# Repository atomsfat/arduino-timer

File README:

Arduino timer
=============
This is a configurable timer using arduino, rtc (DS1307) and a lcd display
For debian and ubuntu install avr-compiler
```js
apt-get install avrdude binutils-avr gcc-avr avr-libc gdb-avr
```
Install eclipse-cpp
Configure the project:
File>Project>Makefile with existing source
Install arduino-022
Change the following in the Makefile
ARDUINO_PATH
AVRDUDE_PORT
AVR_TOOLS_PATH

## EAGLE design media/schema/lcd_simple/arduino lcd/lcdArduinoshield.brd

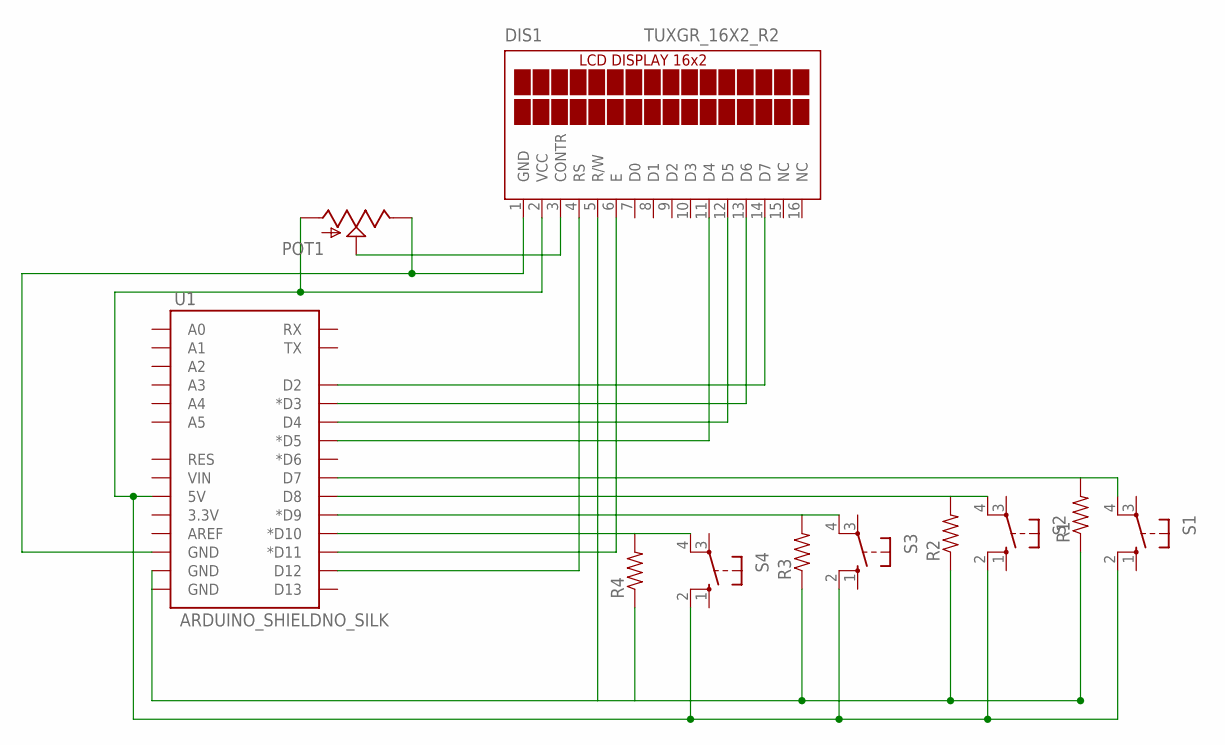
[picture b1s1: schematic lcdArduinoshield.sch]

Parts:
DIS1: TUXGR_16X2_R2
POT1: POT100K_3362U; 3362U
R1, R2, R3, R4: RESISTORPTH-1/4W; AXIAL-0.4
S1, S2, S3, S4: 10-XX; B3F-10XX
U1: ARDUINO_SHIELDNO_SILK; DUEMILANOVE_VIAS

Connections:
+5V: DIS1.2 (VCC), POT1.P$3 (A), S1.2 (S1), S2.2 (S1), S3.2 (S1), S4.2 (S1), U1.5V
GND: DIS1.1 (GND), POT1.P$1 (E), U1.GND@2 (GND)
GND1: DIS1.5 (R/W), R1.P$1 (1), R2.P$1 (1), R3.P$1 (1), R4.P$1 (1), U1.GND@0 (GND), U1.GND@1 (GND)
unnamed: DIS1.14 (D7), U1.D2
unnamed: DIS1.13 (D6), U1.D3 (*D3)
unnamed: DIS1.12 (D5), U1.D4
unnamed: DIS1.11 (D4), U1.D5 (*D5)
unnamed: DIS1.6 (E), U1.D11 (*D11)
unnamed: R4.P$2 (2), S4.4 (P1), U1.D10 (*D10)
unnamed: DIS1.4 (RS), U1.D12
unnamed: R3.P$2 (2), S3.4 (P1), U1.D9 (*D9)
unnamed: R2.P$2 (2), S2.4 (P1), U1.D8
unnamed: R1.P$2 (2), S1.4 (P1), U1.D7
POTDIV: DIS1.3 (CONTR), POT1.P$2 (S)

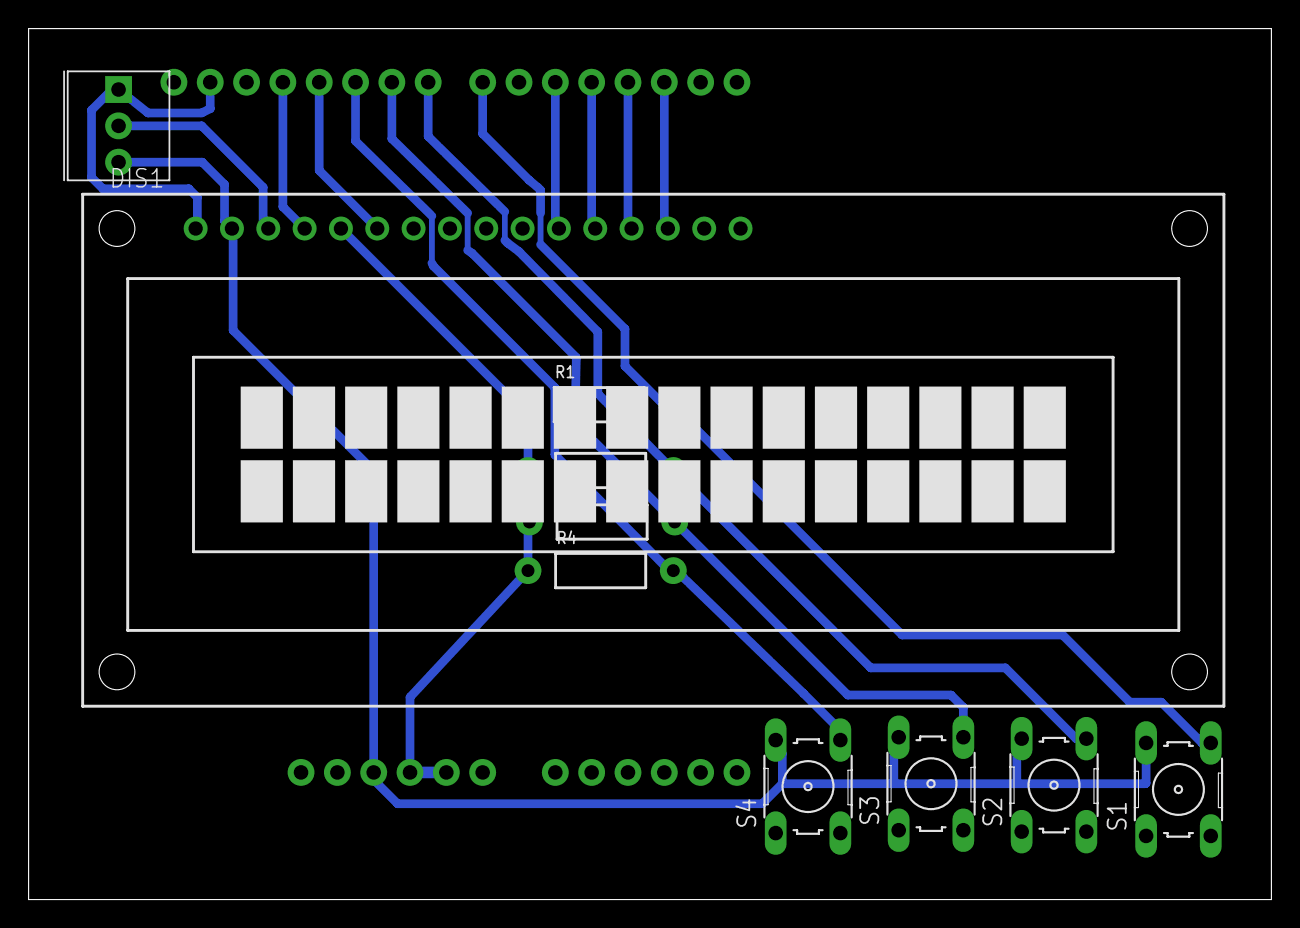
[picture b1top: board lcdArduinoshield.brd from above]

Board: 2 copper layers, 86.9 x 60.9 mm, 11 parts (0 on the bottom side), 14 nets.

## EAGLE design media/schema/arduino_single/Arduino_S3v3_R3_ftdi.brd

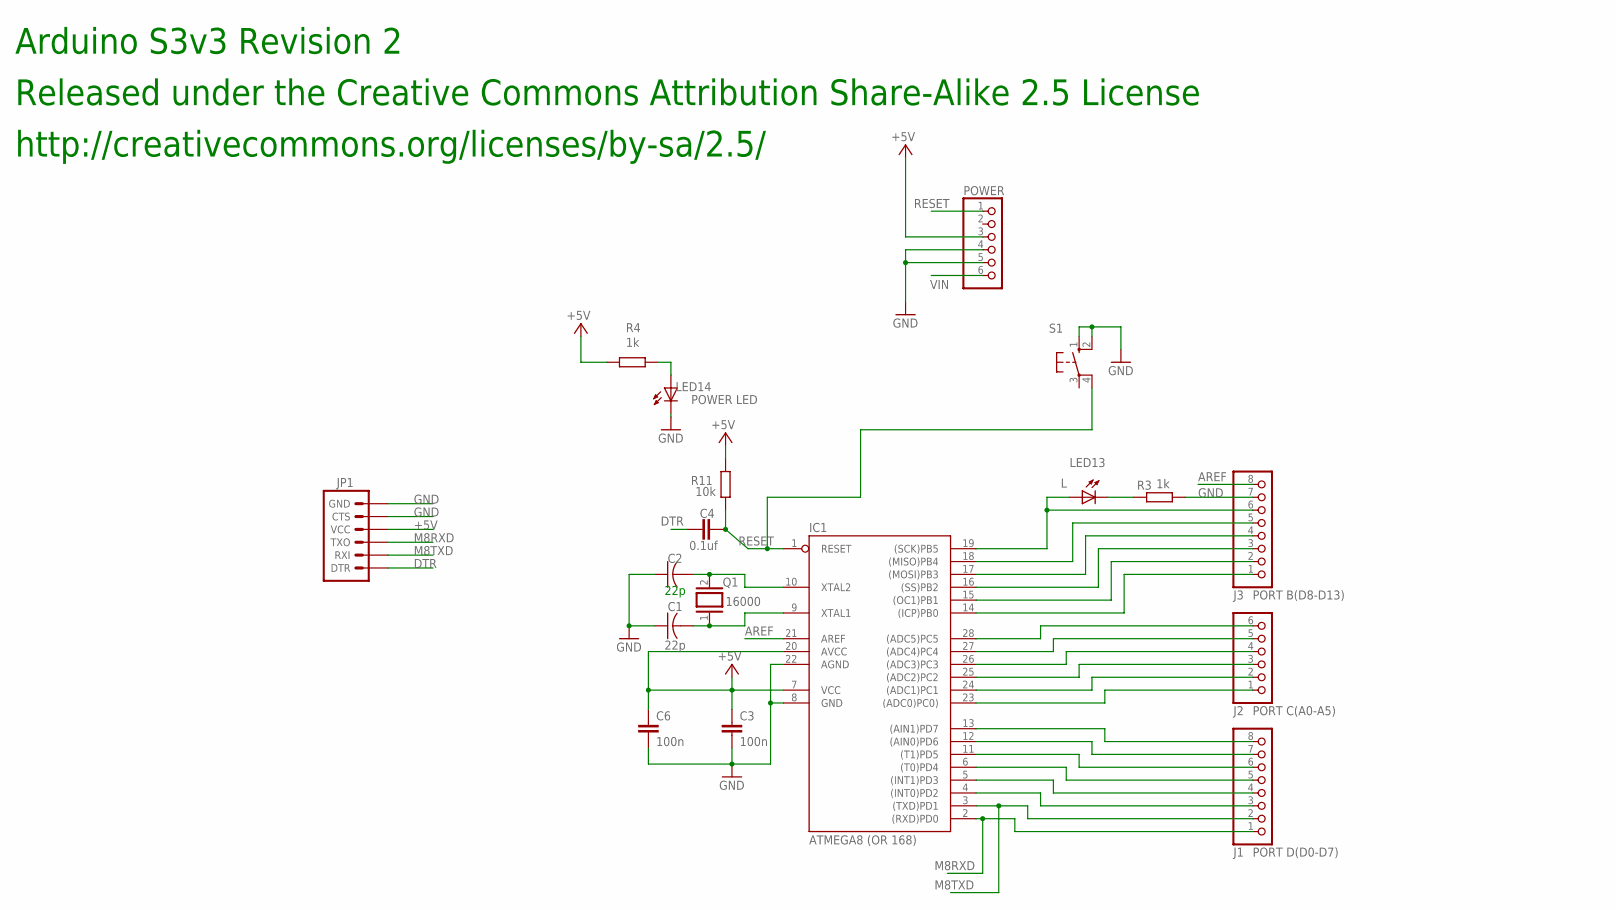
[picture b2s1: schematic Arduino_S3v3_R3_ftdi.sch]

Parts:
C1, C2: 22p; C025-024X044
C3, C6: 100n; C050-025X075
C4: 0.1uf; C050-025X075
IC1: ATMEGA8 (OR 168); DIL28-3
J1: PORT D(D0-D7); 1X08
J2: PORT C(A0-A5); 1X06
J3: PORT B(D8-D13); 1X08
JP1: ARDUINO_SERIAL_PROGRAMLONGPADS; 1X06_LONGPADS
LED13: L; LED3MM
LED14: POWER LED; LED3MM
POWER: PINHD-1X6; 1X06
Q1: 16000; QS
R3, R4: 1k; 0207/10
R11: 10k; 0207/10
S1: 10-XX; B3F-10XX

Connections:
+5V: C3.1, C6.1, IC1.7 (VCC), IC1.20 (AVCC), JP1.4 (VCC), POWER.3, R4.2, R11.2
AREF: IC1.21 (AREF), J3.8
DTR: C4.1, JP1.1 (DTR)
GND: C1.1, C2.1, C3.2, C6.2, IC1.8 (GND), IC1.22 (AGND), J3.7, JP1.5 (CTS), JP1.6 (GND), LED14.K (C), POWER.4, POWER.5, R3.1, S1.1 (S), S1.2 (S1)
M8RXD: IC1.2 ((RXD)PD0), J1.1, JP1.3 (TXO)
M8TXD: IC1.3 ((TXD)PD1), J1.2, JP1.2 (RXI)
unnamed: IC1.18 ((MISO)PB4), J3.5
unnamed: LED14.A, R4.1
unnamed: IC1.17 ((MOSI)PB3), J3.4
unnamed: IC1.14 ((ICP)PB0), J3.1
unnamed: C1.2, IC1.9 (XTAL1), Q1.1
unnamed: C2.2, IC1.10 (XTAL2), Q1.2
unnamed: IC1.4 ((INT0)PD2), J1.3
unnamed: IC1.5 ((INT1)PD3), J1.4
unnamed: IC1.6 ((T0)PD4), J1.5
unnamed: IC1.11 ((T1)PD5), J1.6
unnamed: IC1.12 ((AIN0)PD6), J1.7
unnamed: IC1.13 ((AIN1)PD7), J1.8
unnamed: IC1.23 ((ADC0)PC0)), J2.1
unnamed: IC1.24 ((ADC1)PC1), J2.2
unnamed: IC1.25 ((ADC2)PC2), J2.3
unnamed: IC1.26 ((ADC3)PC3), J2.4
unnamed: IC1.27 ((ADC4)PC4), J2.5
unnamed: IC1.28 ((ADC5)PC5), J2.6
unnamed: IC1.15 ((OC1)PB1), J3.2
unnamed: IC1.16 ((SS)PB2), J3.3
unnamed: LED13.K (C), R3.2
RESET: C4.2, IC1.1 (RESET), POWER.1, R11.1, S1.4 (P1)
SCK: IC1.19 ((SCK)PB5), J3.6, LED13.A
VIN: POWER.6

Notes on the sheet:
Released under the Creative Commons Attribution Share-Alike 2.5 License
http://creativecommons.org/licenses/by-sa/2.5/
Arduino S3v3 Revision 2

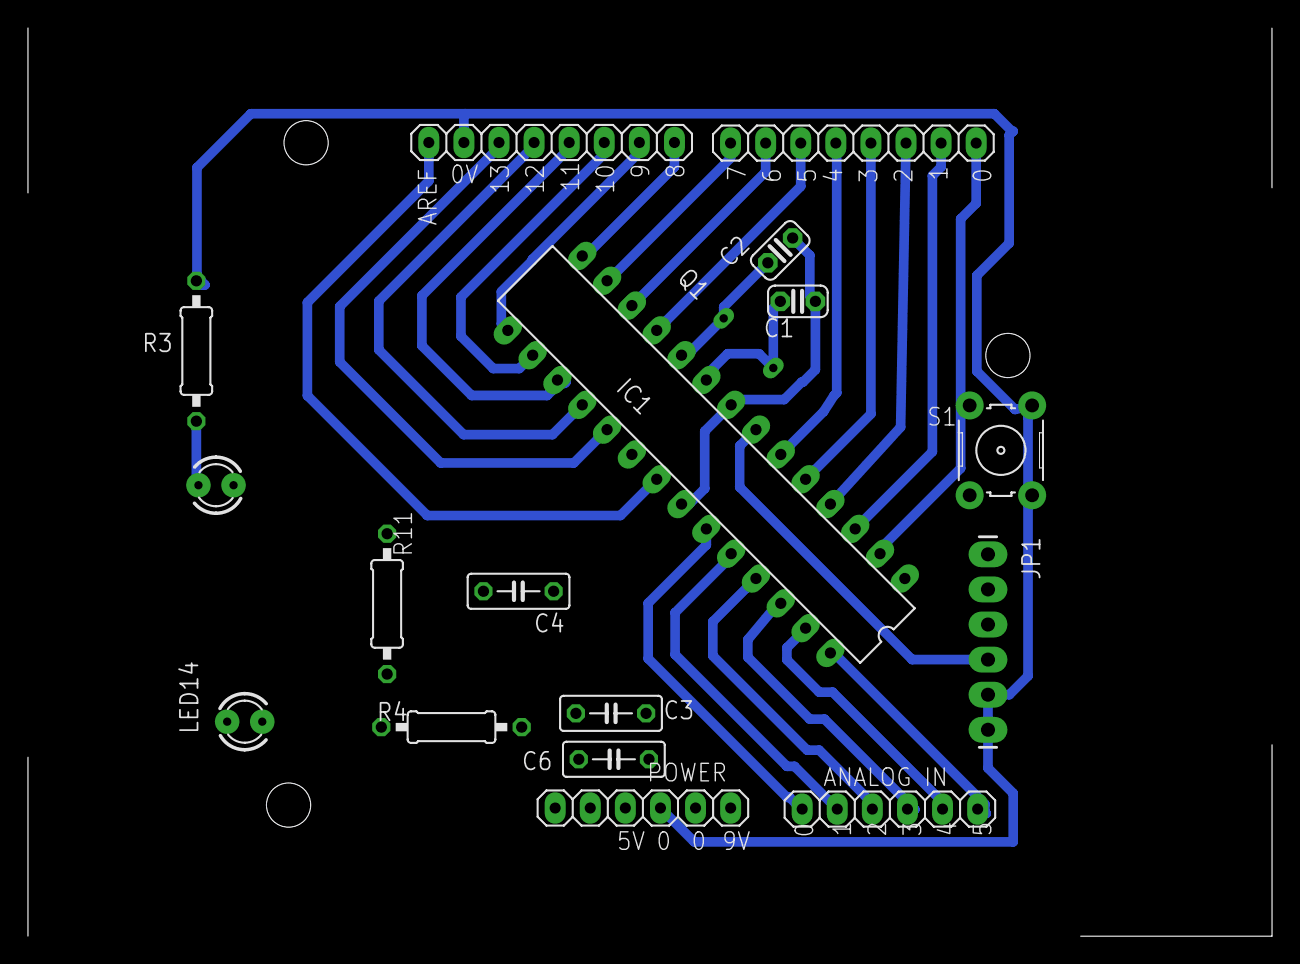
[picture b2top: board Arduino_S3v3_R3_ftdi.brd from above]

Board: 2 copper layers, 90.1 x 65.7 mm, 18 parts (1 on the bottom side), 29 nets.

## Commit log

2011-09-07 first attempt to model and command
2011-09-07 added schema
2011-09-15 added makefile
2011-09-21 added master makefile
2011-09-21 added Makefile for Main.cpp
2011-09-21 remove old makefile
2011-09-21 added functional lines to main
2011-09-22 added gitingnore
2011-09-22 make Makefile ignoreded because it may contain user specific data
2011-09-24 correct makefilecpp
2011-09-24 removed Makefile because it contains current user settings
2011-09-25 servo library
2011-09-25 Added watch dog
2011-09-25 added servo library to makefile
2011-09-28 Added RTC library
2011-09-28 working turn off
2011-10-05 funciona el despliegue de cuanto tiempo esta encendido
2011-10-09 version de linux funcional
2011-10-14 added vector
2011-11-10 1;5S 1;5S
2013-02-18 taking againg this project
2013-02-18 added new schemas
2013-02-18 correcting files
2013-02-18 change cancel button because in pcb is changed
2013-03-21 adding servo
2013-03-25 ignoring some files
2013-03-25 making markdown readme
2013-03-25 Update README.markdown
    more format to makefile
2013-04-01 adding makefile
2013-04-01 trying support for arduino 1.0
2013-04-15 now it compiles on mac
2013-04-15 Removing warning
2013-08-11 changing default home for lcd and modified makefile
2013-08-11 new version make
2013-08-11 adding validation to avoid overflow
2013-08-11 adding new command to handle programing timer
2013-08-12 almost done
2013-08-12 solving problem with char array to short
2013-08-25 Update README.markdown
    Updapting for fedora
2013-08-25 added logic to get dayWeeks for alarm
2013-08-26 saving data to eemprom
2013-08-26 now seems to be working
2013-08-26 small tweak to improve managing time
2013-08-26 solving issues with memory eeprom now it works with ram from ds1307
2013-08-27 testing saving multiple programs
2013-09-09 latest change now it is installed
2013-09-09 now abble to program on for two hours

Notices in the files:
parts and their libraries:
SparkFun: Licensing: CC v3.0 Share-Alike You are welcome to use this library for commercial purposes.
